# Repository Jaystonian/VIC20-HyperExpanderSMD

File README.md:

# VIC20-HyperExpanderSMD
A redesign of the HyperExpander due to the parts availability sourcing issues of 2022

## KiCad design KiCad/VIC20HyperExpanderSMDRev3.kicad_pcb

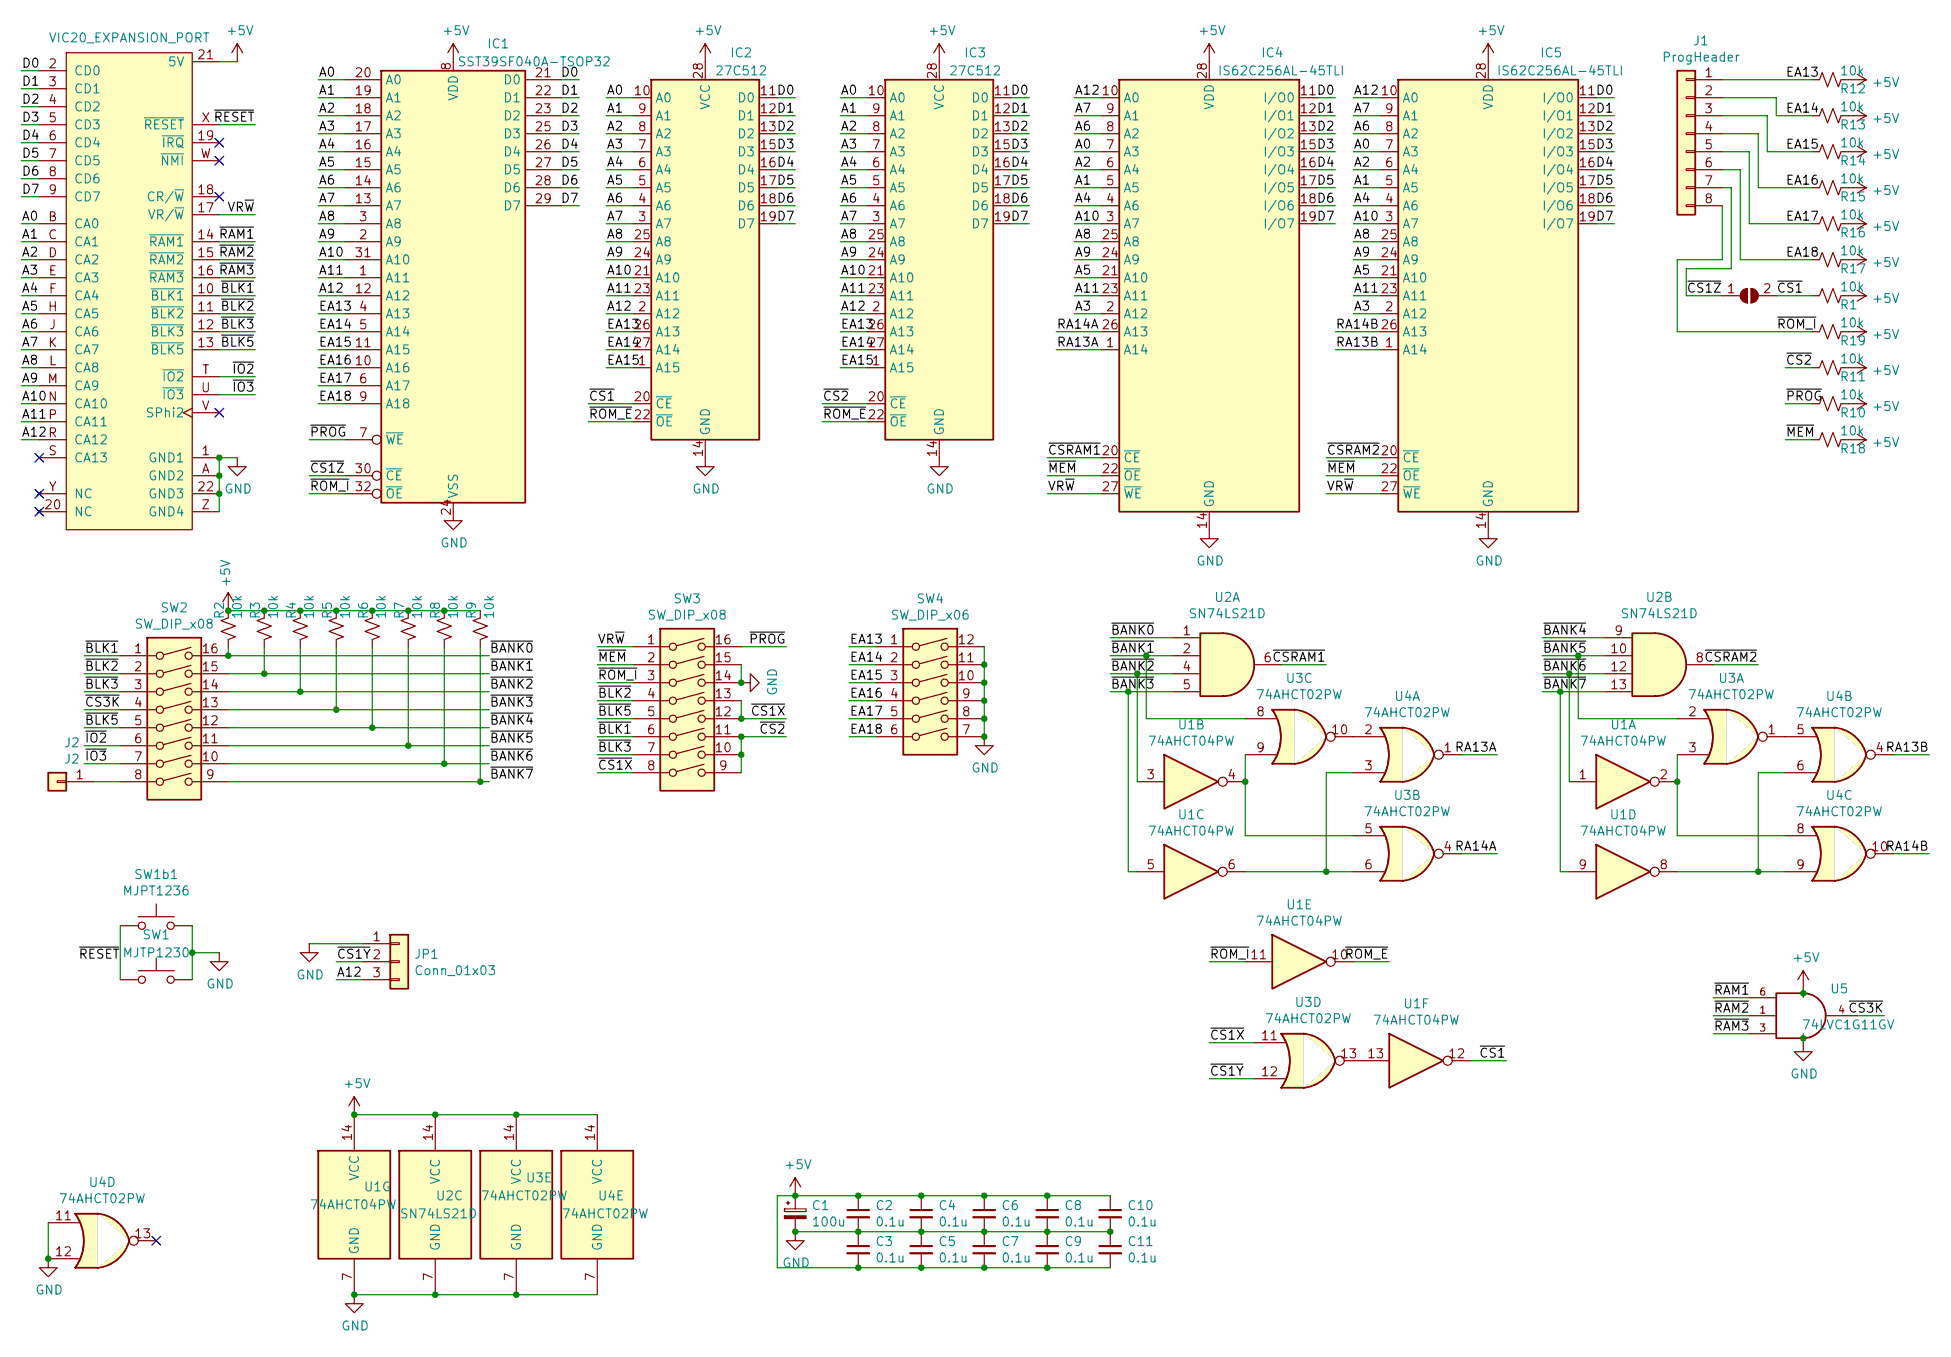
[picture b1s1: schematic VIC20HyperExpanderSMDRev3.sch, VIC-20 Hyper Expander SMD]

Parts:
C1: 100u; CP_Radial_D8.0mm_P3.50mm
C2, C3, C4, C5, C6, C7, C8, C9, C10, C11: 0.1u; C_0603_1608Metric_Pad1.05x0.95mm_HandSolder
IC1: SST39SF040A-TSOP32; TSOP-32_14x8mm_P0.5mm
IC2, IC3: 27C512; DIP-28_W15.24mm_Socket
IC4, IC5: IS62C256AL-45TLI
J1: ProgHeader; PinSocket_1x08_P2.54mm_Vertical
J2: J2; PinHeader_1x01_P1.27mm_Vertical
JP1: Conn_01x03; PinHeader_1x03_P2.54mm_Vertical
R1, R2, R3, R4, R5, R6, R7, R8, R9, R10, R11, R12, R13, R14, R15, R16, R17, R18, R19: 10k; R_0805_2012Metric_Pad1.15x1.40mm_HandSolder
SJ1: SolderJumper_2_Open; SolderJumper-2_P1.3mm_Open_TrianglePad1.0x1.5mm
SW1: MJTP1230; SW_PUSH_6mm_H8mm
SW1b1: MJPT1236; SW_Tactile_SPST_Angled_PTS645Vx83-2LFS
SW2, SW3: SW_DIP_x08; SW_DIP_SPSTx08_Slide_9.78x22.5mm_W7.62mm_P2.54mm
SW4: SW_DIP_x06; SW_DIP_SPSTx06_Slide_9.78x17.42mm_W7.62mm_P2.54mm
U1: 74AHCT04PW; TSSOP-14_4.4x5mm_P0.65mm
U2: SN74LS21D; SOIC-14_3.9x8.7mm_P1.27mm
U3, U4: 74AHCT02PW; TSSOP-14_4.4x5mm_P0.65mm
U5: 74LVC1G11GV; SuperSOT-6
X1: VIC20_EXPANSION_PORT; VIC20_EXPANSION_CARD_sven

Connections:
+5V: C1.1, C2.1, C3.2, C4.1, C5.2, C6.1, C7.2, C8.1, C9.2, C10.1, C11.2, IC1.8 (VDD), IC2.28 (VCC), IC3.28 (VCC), IC4.28 (VDD), IC5.28 (VDD), R1.1, R2.1, R3.1, R4.1, R5.1, R6.1, R7.1, R8.1, R9.1, R10.1, R11.1, R12.1, R13.1, R14.1, R15.1, R16.1, R17.1, R18.1, R19.1, U1.14 (VCC), U2.14 (VCC), U3.14 (VCC), U4.14 (VCC), U5.5 (VCC), X1.21 (5V)
/A0: IC1.20 (A0), IC2.10 (A0), IC3.10 (A0), IC4.7 (A3), IC5.7 (A3), X1.B (CA0)
/A1: IC1.19 (A1), IC2.9 (A1), IC3.9 (A1), IC4.5 (A5), IC5.5 (A5), X1.C (CA1)
/A2: IC1.18 (A2), IC2.8 (A2), IC3.8 (A2), IC4.6 (A4), IC5.6 (A4), X1.D (CA2)
/A3: IC1.17 (A3), IC2.7 (A3), IC3.7 (A3), IC4.2 (A12), IC5.2 (A12), X1.E (CA3)
/A4: IC1.16 (A4), IC2.6 (A4), IC3.6 (A4), IC4.4 (A6), IC5.4 (A6), X1.F (CA4)
/A5: IC1.15 (A5), IC2.5 (A5), IC3.5 (A5), IC4.21 (A10), IC5.21 (A10), X1.H (CA5)
/A6: IC1.14 (A6), IC2.4 (A6), IC3.4 (A6), IC4.8 (A2), IC5.8 (A2), X1.J (CA6)
/A7: IC1.13 (A7), IC2.3 (A7), IC3.3 (A7), IC4.9 (A1), IC5.9 (A1), X1.K (CA7)
/A8: IC1.3 (A8), IC2.25 (A8), IC3.25 (A8), IC4.25 (A8), IC5.25 (A8), X1.L (CA8)
/A9: IC1.2 (A9), IC2.24 (A9), IC3.24 (A9), IC4.24 (A9), IC5.24 (A9), X1.M (CA9)
/A10: IC1.31 (A10), IC2.21 (A10), IC3.21 (A10), IC4.3 (A7), IC5.3 (A7), X1.N (CA10)
/A11: IC1.1 (A11), IC2.23 (A11), IC3.23 (A11), IC4.23 (A11), IC5.23 (A11), X1.P (CA11)
/A12: IC1.12 (A12), IC2.2 (A12), IC3.2 (A12), IC4.10 (A0), IC5.10 (A0), JP1.3, X1.R (CA12)
/D0: IC1.21 (D0), IC2.11 (D0), IC3.11 (D0), IC4.11 (I/O0), IC5.11 (I/O0), X1.2 (CD0)
/D1: IC1.22 (D1), IC2.12 (D1), IC3.12 (D1), IC4.12 (I/O1), IC5.12 (I/O1), X1.3 (CD1)
/D2: IC1.23 (D2), IC2.13 (D2), IC3.13 (D2), IC4.13 (I/O2), IC5.13 (I/O2), X1.4 (CD2)
/D3: IC1.25 (D3), IC2.15 (D3), IC3.15 (D3), IC4.15 (I/O3), IC5.15 (I/O3), X1.5 (CD3)
/D4: IC1.26 (D4), IC2.16 (D4), IC3.16 (D4), IC4.16 (I/O4), IC5.16 (I/O4), X1.6 (CD4)
/D5: IC1.27 (D5), IC2.17 (D5), IC3.17 (D5), IC4.17 (I/O5), IC5.17 (I/O5), X1.7 (CD5)
/D6: IC1.28 (D6), IC2.18 (D6), IC3.18 (D6), IC4.18 (I/O6), IC5.18 (I/O6), X1.8 (CD6)
/D7: IC1.29 (D7), IC2.19 (D7), IC3.19 (D7), IC4.19 (I/O7), IC5.19 (I/O7), X1.9 (CD7)
/EA13: IC1.4 (A13), IC2.26 (A13), IC3.26 (A13), J1.1, R12.2, SW4.1
/EA14: IC1.5 (A14), IC2.27 (A14), IC3.27 (A14), J1.2, R13.2, SW4.2
/EA15: IC1.11 (A15), IC2.1 (A15), IC3.1 (A15), J1.3, R14.2, SW4.3
/EA16: IC1.10 (A16), J1.4, R15.2, SW4.4
/EA17: IC1.6 (A17), J1.5, R16.2, SW4.5
/EA18: IC1.9 (A18), J1.6, R17.2, SW4.6
/RA13A: IC4.1 (A14), U4.1
/RA13B: IC5.1 (A14), U4.4
/RA14A: IC4.26 (A13), U3.4
/RA14B: IC5.26 (A13), U4.10
/VR~W: IC4.27 (~WE), IC5.27 (~WE), SW3.1, X1.17 (VR/~W~)
/~BANK0: R2.2, SW2.16, U2.1
/~BANK1: R3.2, SW2.15, U2.2, U3.8
/~BANK2: R4.2, SW2.14, U1.3, U2.4
/~BANK3: R5.2, SW2.13, U1.5, U2.5
/~BANK4: R6.2, SW2.12, U2.9
/~BANK5: R7.2, SW2.11, U2.10, U3.2
/~BANK6: R8.2, SW2.10, U1.1, U2.12
/~BANK7: R9.2, SW2.9, U1.9, U2.13
/~BLK1: SW2.1, SW3.6, X1.10 (~BLK1~)
/~BLK2: SW2.2, SW3.4, X1.11 (~BLK2~)
/~BLK3: SW2.3, SW3.7, X1.12 (~BLK3~)
/~BLK5: SW2.5, SW3.5, X1.13 (~BLK5~)
/~CS1: IC2.20 (~CE), R1.2, SJ1.2 (B), U1.12
/~CS1X: SW3.8, SW3.12, SW3.13, U3.11
/~CS1Y: JP1.2, U3.12
/~CS1Z: IC1.30 (~CE), J1.7, SJ1.1 (A)
/~CS2: IC3.20 (~CE), R11.2, SW3.9, SW3.10, SW3.11
/~CS3K: SW2.4, U5.4
/~CSRAM1: IC4.20 (~CE), U2.6
/~CSRAM2: IC5.20 (~CE), U2.8
/~IO2: SW2.6, X1.T (~IO2)
/~IO3: SW2.7, X1.U (~IO3)
/~MEM: IC4.22 (~OE), IC5.22 (~OE), R18.2, SW3.2
/~PROG: IC1.7 (~WE), R10.2, SW3.16
/~RAM1: U5.6, X1.14 (~RAM1~)
/~RAM2: U5.1, X1.15 (~RAM2~)
/~RAM3: U5.3, X1.16 (~RAM3~)
/~RESET: SW1.1, SW1b1.1, X1.X (~RESET~)
/~ROM_E: IC2.22 (~OE), IC3.22 (~OE), U1.10
/~ROM_I: IC1.32 (~OE), J1.8, R19.2, SW3.3, U1.11
GND: C1.2, C2.2, C3.1, C4.2, C5.1, C6.2, C7.1, C8.2, C9.1, C10.2, C11.1, IC1.24 (VSS), IC2.14 (GND), IC3.14 (GND), IC4.14 (GND), IC5.14 (GND), JP1.1, SW1.2, SW1b1.2, SW3.14, SW3.15, SW4.7, SW4.8, SW4.9, SW4.10, SW4.11, SW4.12, U1.7 (GND), U2.7 (GND), U3.7 (GND), U4.7 (GND), U4.11, U4.12, U5.2 (GND), X1.1 (GND1), X1.22 (GND3), X1.A (GND2), X1.Z (GND4)
unnamed: J2.1, SW2.8
unnamed: U1.2, U3.3, U4.8
unnamed: U1.4, U3.5, U3.9
unnamed: U1.6, U3.6, U4.3
unnamed: U1.8, U4.6, U4.9
unnamed: U1.13, U3.13
unnamed: U3.1, U4.5
unnamed: U3.10, U4.2

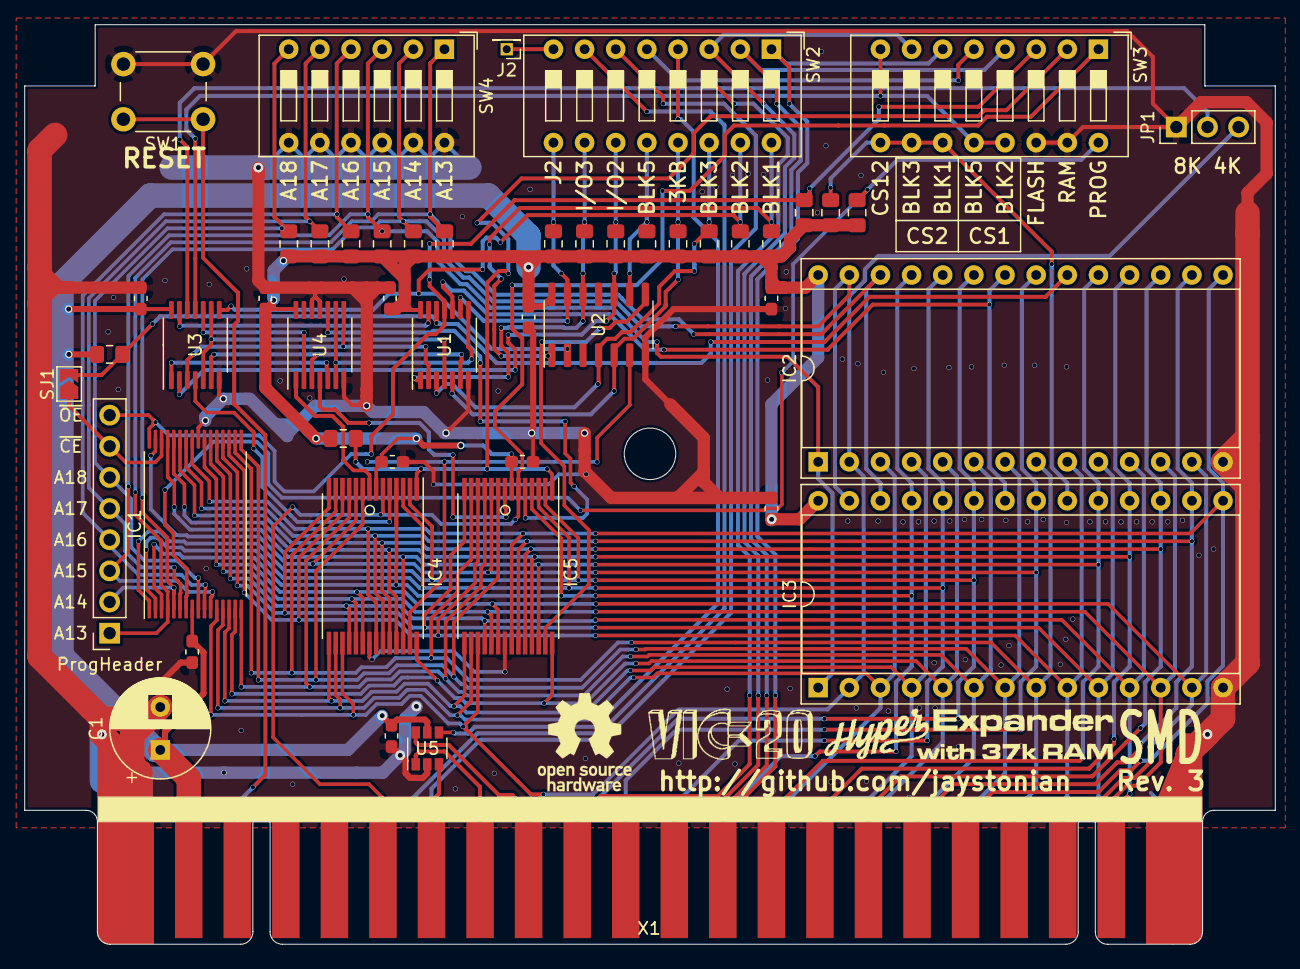
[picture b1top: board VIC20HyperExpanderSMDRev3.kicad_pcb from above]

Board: 2 copper layers, 102.0 x 75.0 mm, 49 parts (0 on the bottom side), 72 nets.

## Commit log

2025-05-11 Apps and games included
